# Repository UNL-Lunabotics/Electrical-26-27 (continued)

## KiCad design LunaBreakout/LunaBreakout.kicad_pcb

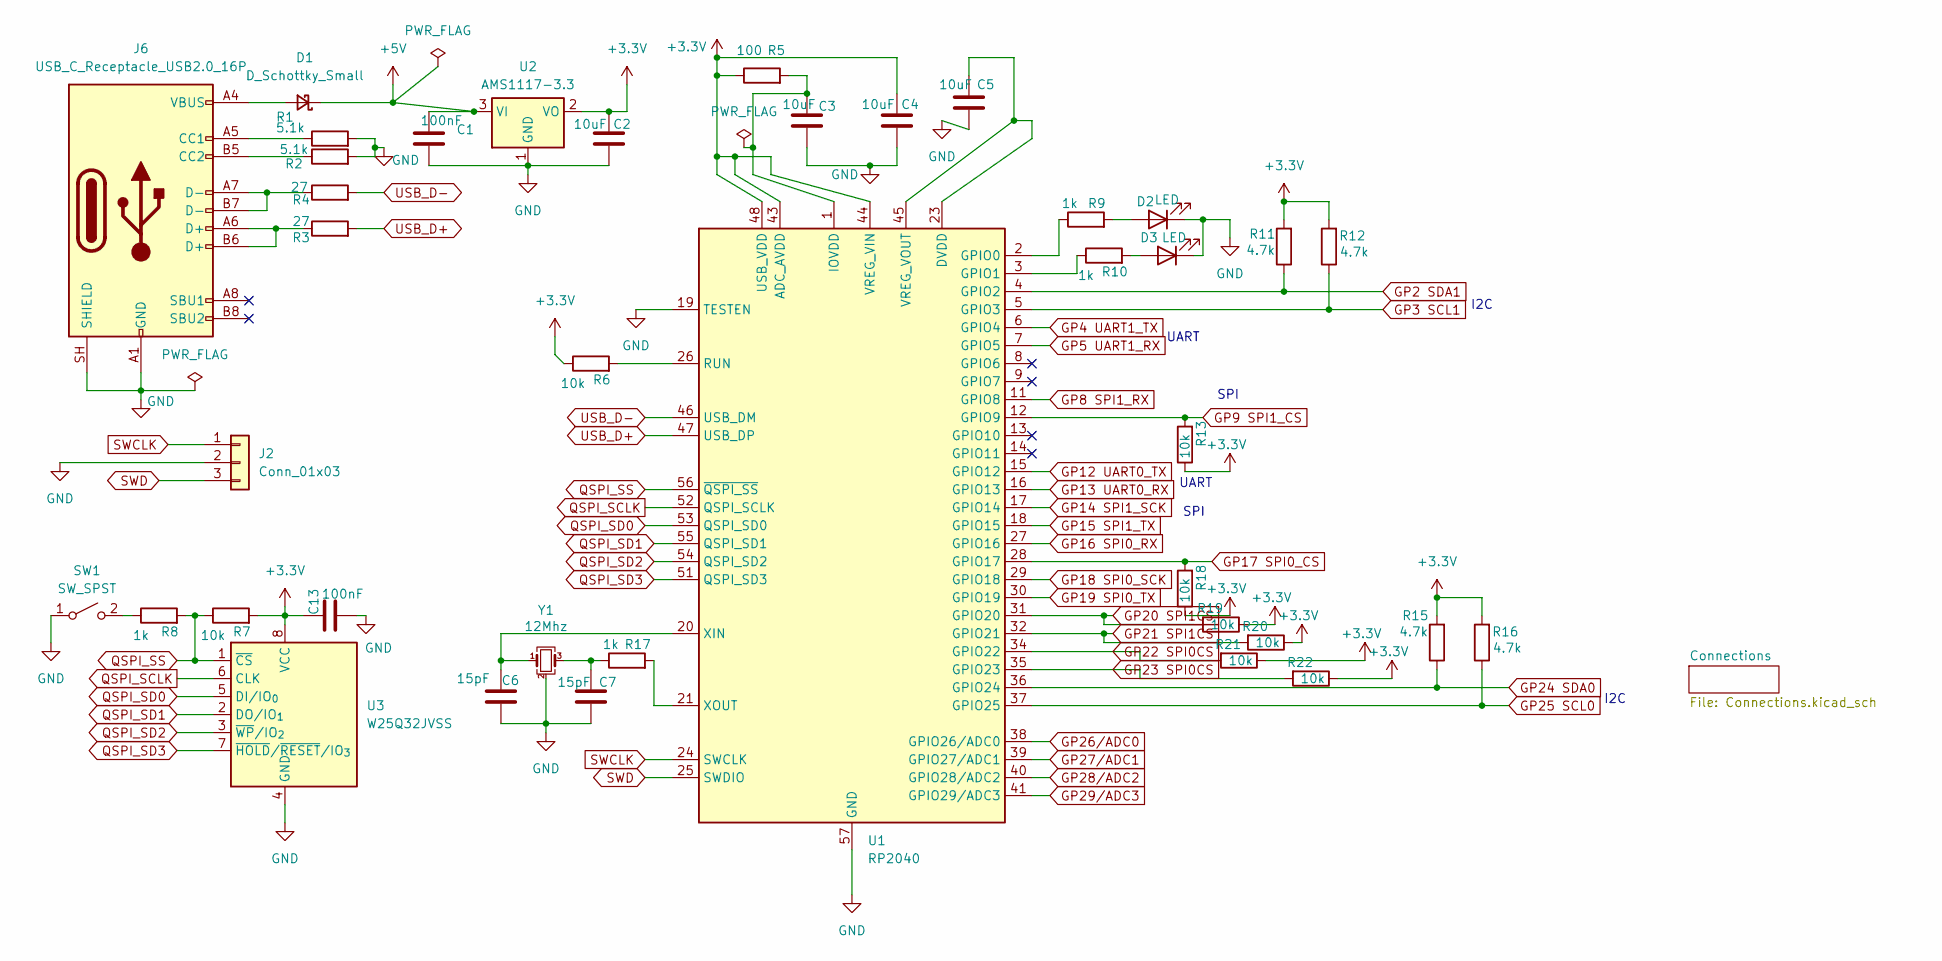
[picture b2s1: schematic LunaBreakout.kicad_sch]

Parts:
C1, C13: 100nF; C_0805_2012Metric
C2, C3, C4, C5: 10uF; C_0805_2012Metric
C6, C7: 15pF; C_0805_2012Metric
D1: D_Schottky_Small; D_SMA
D2, D3: LED; LED_0805_2012Metric
J2: Conn_01x03; JST_XH_B3B-XH-A_1x03_P2.50mm_Vertical
J6: USB_C_Receptacle_USB2.0_16P; USB_C_Receptacle_XKB_U262-16XN-4BVC11
R1, R2: 5.1k; R_0805_2012Metric
R3, R4: 27; R_0805_2012Metric
R5: 100; R_0805_2012Metric
R6, R7, R13, R18, R19, R20, R21, R22: 10k; R_0805_2012Metric
R8, R9, R10, R17: 1k; R_0805_2012Metric
R11, R12, R15, R16: 4.7k; R_0805_2012Metric
SW1: SW_SPST; SW_SPST_CK_RS282G05A3
U1: RP2040; QFN-56-1EP_7x7mm_P0.4mm_EP3.2x3.2mm
U2: AMS1117-3.3; SOT-223-3_TabPin2
U3: W25Q32JVSS; WSON-8-1EP_4x4mm_P0.8mm_EP2.2x3mm
Y1: 12Mhz; Crystal_SMD_SeikoEpson_FA238V-4Pin_3.2x2.5mm

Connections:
+3.3V: C2.1, C4.1, C13.1, R5.1, R6.1, R7.2, R11.2, R12.2, R13.1, R15.2, R16.2, R18.1, R19.1, R20.1, R21.1, R22.1, U1.43 (ADC_AVDD), U1.44 (VREG_VIN), U1.48 (USB_VDD), U2.2 (VO), U3.8 (VCC); also elsewhere on the board
+5V: C1.1, D1.1 (K), U2.3 (VI)
GND: C1.2, C2.2, C3.2, C4.2, C5.2, C6.2, C7.2, C13.2, D2.1 (K), D3.1 (K), J2.2, J6.A1 (GND), J6.A12 (GND), J6.B1 (GND), J6.B12 (GND), J6.SH (SHIELD), R1.2, R2.2, SW1.1 (A), U1.19 (TESTEN), U1.57 (GND), U2.1 (GND), U3.4 (GND), Y1.2 (G), Y1.4 (G); also elsewhere on the board
GP2 SDA1: R11.1, U1.4 (GPIO2); also elsewhere on the board
GP3 SCL1: R12.1, U1.5 (GPIO3); also elsewhere on the board
GP4 UART1_TX: U1.6 (GPIO4); also elsewhere on the board
GP5 UART1_RX: U1.7 (GPIO5); also elsewhere on the board
GP8 SPI1_RX: U1.11 (GPIO8); also elsewhere on the board
GP9 SPI1_CS: R13.2, U1.12 (GPIO9); also elsewhere on the board
GP12 UART0_TX: U1.15 (GPIO12); also elsewhere on the board
GP13 UART0_RX: U1.16 (GPIO13); also elsewhere on the board
GP14 SPI1_SCK: U1.17 (GPIO14); also elsewhere on the board
GP15 SPI1_TX: U1.18 (GPIO15); also elsewhere on the board
GP16 SPI0_RX: U1.27 (GPIO16); also elsewhere on the board
GP17 SPI0_CS: R18.2, U1.28 (GPIO17); also elsewhere on the board
GP18 SPI0_SCK: U1.29 (GPIO18); also elsewhere on the board
GP19 SPI0_TX: U1.30 (GPIO19); also elsewhere on the board
GP20 SPI1CS: R19.2, U1.31 (GPIO20); also elsewhere on the board
GP21 SPI1CS: R20.2, U1.32 (GPIO21); also elsewhere on the board
GP22 SPI0CS: R21.2, U1.34 (GPIO22); also elsewhere on the board
GP23 SPI0CS: R22.2, U1.35 (GPIO23); also elsewhere on the board
GP24 SDA0: R15.1, U1.36 (GPIO24); also elsewhere on the board
GP25 SCL0: R16.1, U1.37 (GPIO25); also elsewhere on the board
GP26/ADC0: U1.38 (GPIO26/ADC0); also elsewhere on the board
GP27/ADC1: U1.39 (GPIO27/ADC1); also elsewhere on the board
GP28/ADC2: U1.40 (GPIO28/ADC2); also elsewhere on the board
GP29/ADC3: U1.41 (GPIO29/ADC3); also elsewhere on the board
unnamed: C3.1, R5.2, U1.1 (IOVDD), U1.10 (IOVDD), U1.22 (IOVDD), U1.33 (IOVDD), U1.42 (IOVDD), U1.49 (IOVDD)
unnamed: C7.1, R17.1, Y1.3
unnamed: D1.2 (A), J6.A4 (VBUS), J6.A9 (VBUS), J6.B4 (VBUS), J6.B9 (VBUS)
unnamed: D2.2 (A), R9.2
unnamed: D3.2 (A), R10.2
unnamed: J6.A5 (CC1), R1.1
unnamed: J6.B5 (CC2), R2.1
unnamed: J6.A6 (D+), J6.B6 (D+), R3.1
unnamed: J6.A7 (D-), J6.B7 (D-), R4.1
unnamed: R8.1, SW1.2 (B)
unnamed: R9.1, U1.2 (GPIO0)
unnamed: R10.1, U1.3 (GPIO1)
unnamed: R6.2, U1.26 (RUN)
unnamed: C5.1, U1.23 (DVDD), U1.45 (VREG_VOUT), U1.50 (DVDD)
unnamed: C6.1, U1.20 (XIN), Y1.1
unnamed: R17.2, U1.21 (XOUT)
QSPI_SCLK: U1.52 (QSPI_SCLK), U3.6 (CLK)
QSPI_SD0: U1.53 (QSPI_SD0), U3.5 (DI/IO_{0})
QSPI_SD1: U1.55 (QSPI_SD1), U3.2 (DO/IO_{1})
QSPI_SD2: U1.54 (QSPI_SD2), U3.3 (~WP/IO_{2})
QSPI_SD3: U1.51 (QSPI_SD3), U3.7 (~HOLD/~RESET/IO_{3})
QSPI_SS: R7.1, R8.2, U1.56 (~QSPI_SS), U3.1 (~CS)
SWCLK: J2.1, U1.24 (SWCLK)
SWD: J2.3, U1.25 (SWDIO)
USB_D+: R3.2, U1.47 (USB_DP)
USB_D-: R4.2, U1.46 (USB_DM)

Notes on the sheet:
I2C
SPI
UART

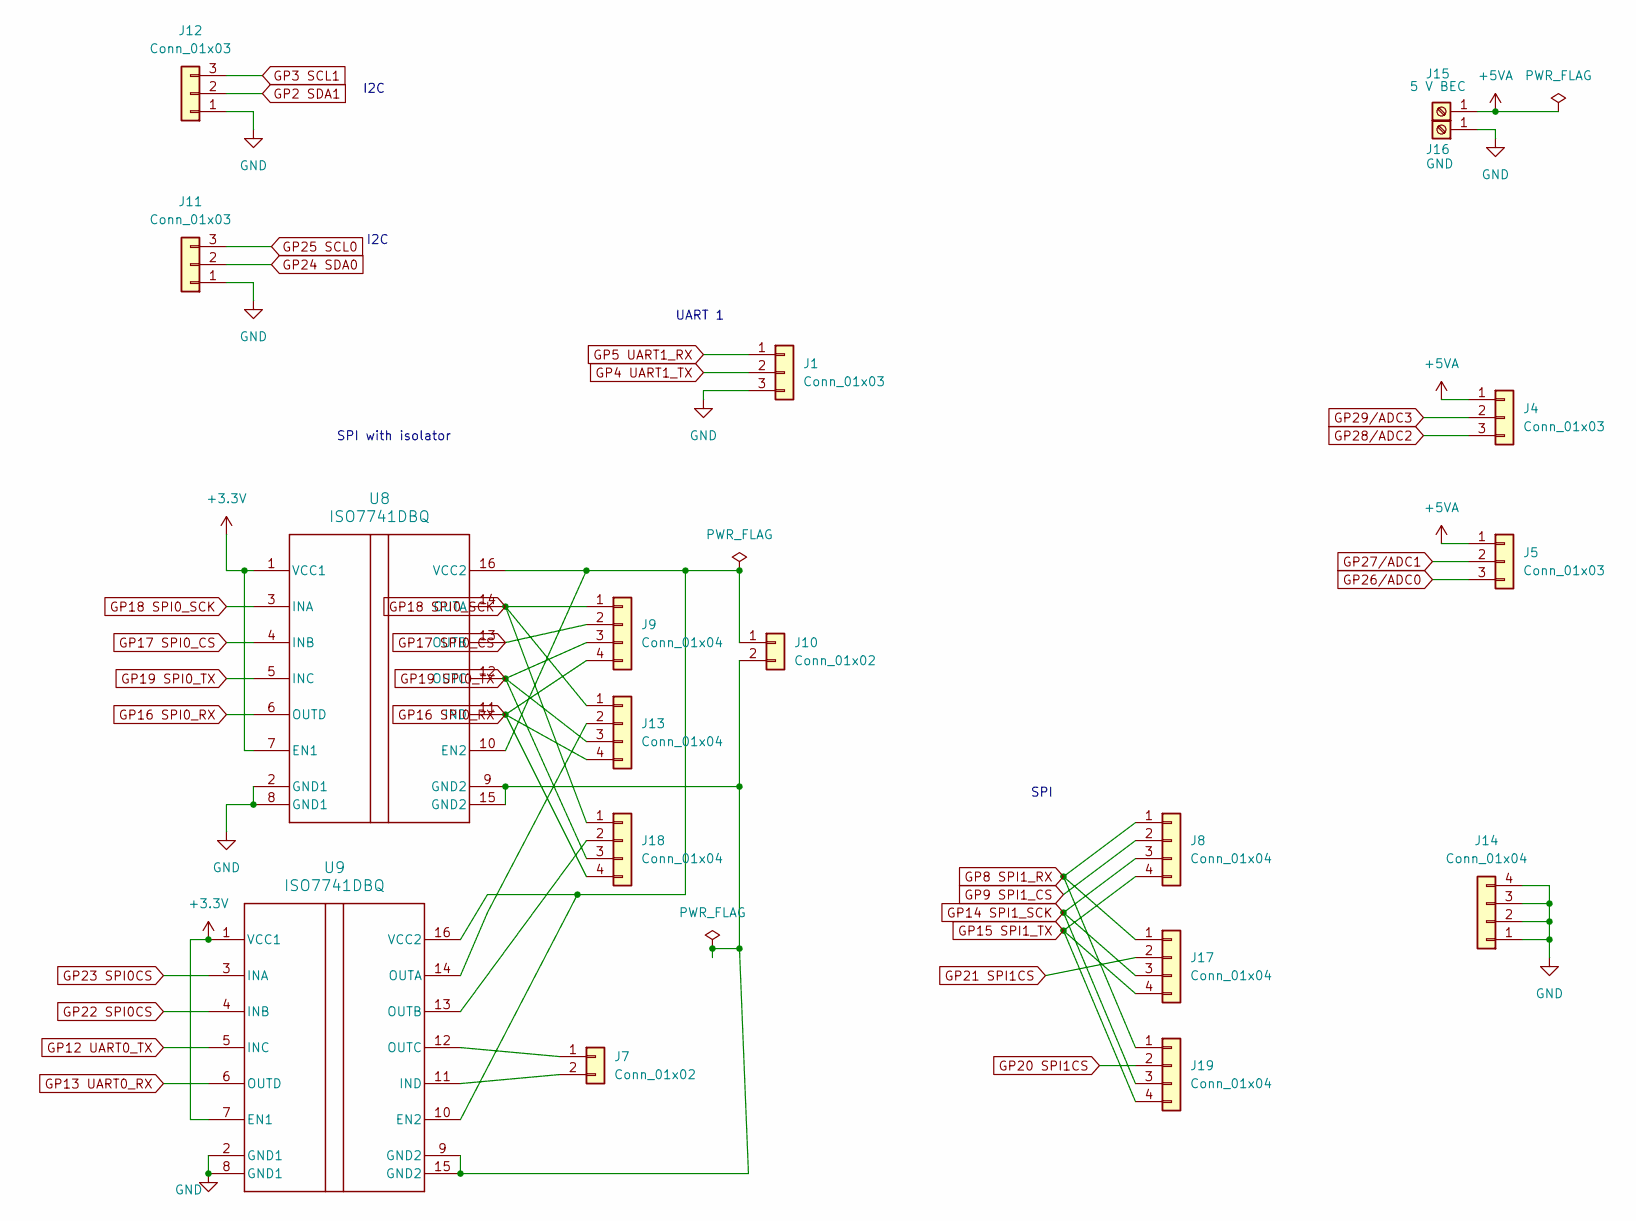
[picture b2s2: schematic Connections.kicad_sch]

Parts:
J1, J4, J5, J11, J12: Conn_01x03; JST_XH_B3B-XH-A_1x03_P2.50mm_Vertical
J7, J10: Conn_01x02; JST_XH_B2B-XH-A_1x02_P2.50mm_Vertical
J8, J9, J13, J14, J17, J18, J19: Conn_01x04; JST_XH_B4B-XH-A_1x04_P2.50mm_Vertical
J15: 5 V BEC; Amphenol_Anytek_AMT0440008DB0000G
J16: GND; Amphenol_Anytek_AMT0440008DB0000G
U8, U9: ISO7741DBQ; DBQ0016A_N

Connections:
+3.3V: U8.1 (VCC1), U8.7 (EN1), U9.1 (VCC1), U9.7 (EN1); also elsewhere on the board
+5VA: J4.1, J5.1, J15.1 (Pin_1_1)
GND: J1.3, J11.1, J12.1, J14.1, J14.2, J14.3, J14.4, J16.1 (Pin_1_1), U8.2 (GND1), U8.8 (GND1), U9.2 (GND1), U9.8 (GND1); also elsewhere on the board
GP2 SDA1: J12.2; also elsewhere on the board
GP3 SCL1: J12.3; also elsewhere on the board
GP4 UART1_TX: J1.2; also elsewhere on the board
GP5 UART1_RX: J1.1; also elsewhere on the board
GP8 SPI1_RX: J8.1, J17.1, J19.1; also elsewhere on the board
GP9 SPI1_CS: J8.2; also elsewhere on the board
GP12 UART0_TX: U9.5 (INC); also elsewhere on the board
GP13 UART0_RX: U9.6 (OUTD); also elsewhere on the board
GP14 SPI1_SCK: J8.3, J17.3, J19.3; also elsewhere on the board
GP15 SPI1_TX: J8.4, J17.4, J19.4; also elsewhere on the board
GP16 SPI0_RX: J9.4, J13.4, J18.4, U8.6 (OUTD), U8.11 (IND); also elsewhere on the board
GP17 SPI0_CS: J9.2, U8.4 (INB), U8.13 (OUTB); also elsewhere on the board
GP18 SPI0_SCK: J9.1, J13.1, J18.1, U8.3 (INA), U8.14 (OUTA); also elsewhere on the board
GP19 SPI0_TX: J9.3, J13.3, J18.3, U8.5 (INC), U8.12 (OUTC); also elsewhere on the board
GP20 SPI1CS: J19.2; also elsewhere on the board
GP21 SPI1CS: J17.2; also elsewhere on the board
GP22 SPI0CS: U9.4 (INB); also elsewhere on the board
GP23 SPI0CS: U9.3 (INA); also elsewhere on the board
GP24 SDA0: J11.2; also elsewhere on the board
GP25 SCL0: J11.3; also elsewhere on the board
GP26/ADC0: J5.3; also elsewhere on the board
GP27/ADC1: J5.2; also elsewhere on the board
GP28/ADC2: J4.3; also elsewhere on the board
GP29/ADC3: J4.2; also elsewhere on the board
unnamed: J7.1, U9.12 (OUTC)
unnamed: J7.2, U9.11 (IND)
unnamed: J10.1, U8.10 (EN2), U8.16 (VCC2), U9.10 (EN2), U9.16 (VCC2)
unnamed: J10.2, U8.9 (GND2), U8.15 (GND2), U9.9 (GND2), U9.15 (GND2)
unnamed: J13.2, U9.14 (OUTA)
unnamed: J18.2, U9.13 (OUTB)

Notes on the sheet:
SPI
SPI with isolator
I2C
UART 1

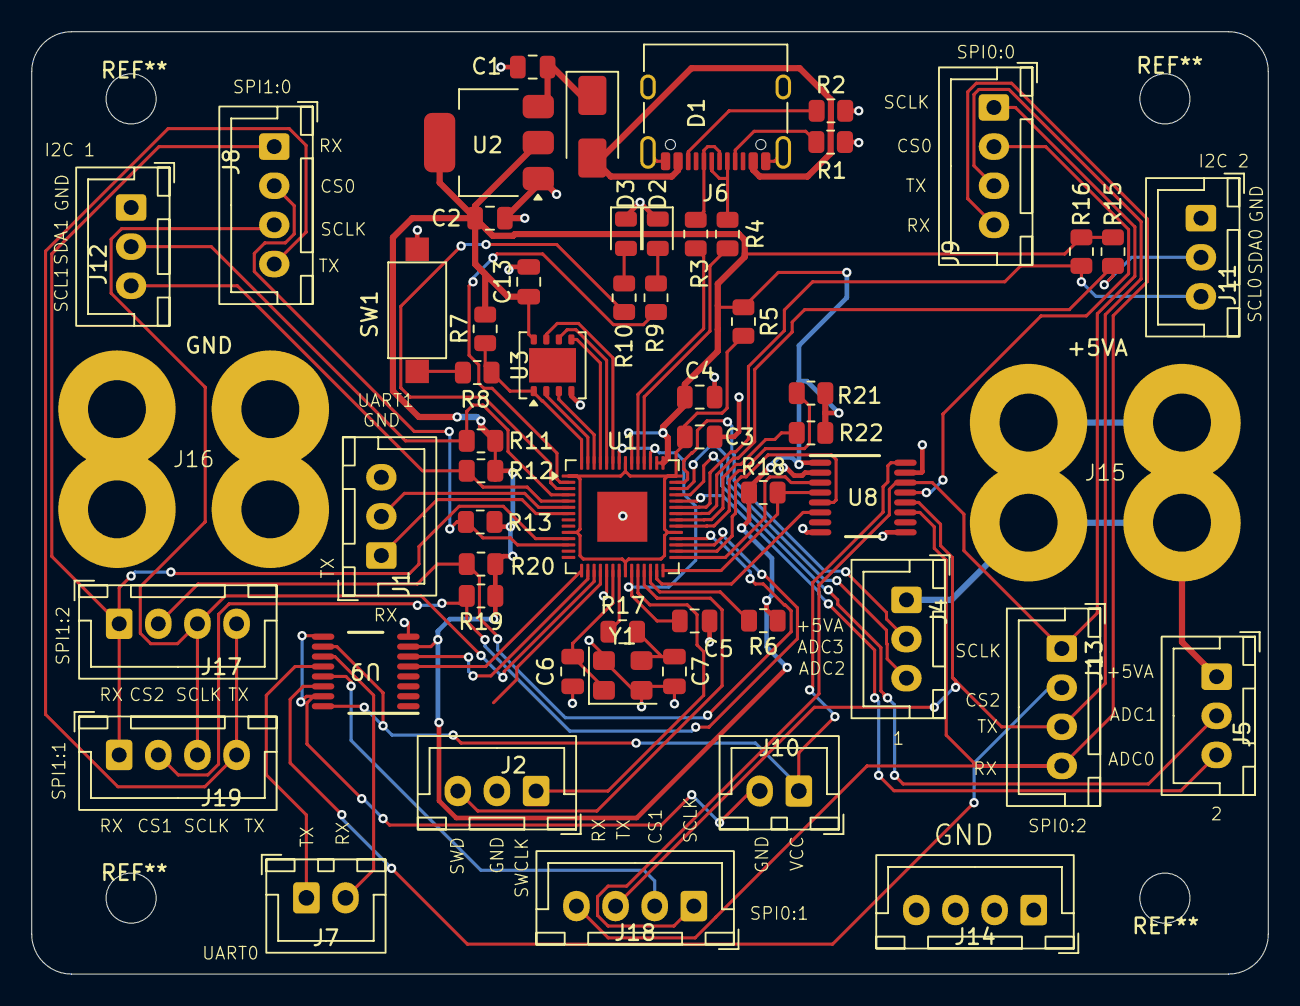
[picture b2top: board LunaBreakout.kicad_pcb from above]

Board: 2 copper layers, 79.0 x 60.2 mm, 57 parts (0 on the bottom side), 60 nets.
